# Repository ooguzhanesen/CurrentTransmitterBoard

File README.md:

# Current Transmitter Board
## Board Features

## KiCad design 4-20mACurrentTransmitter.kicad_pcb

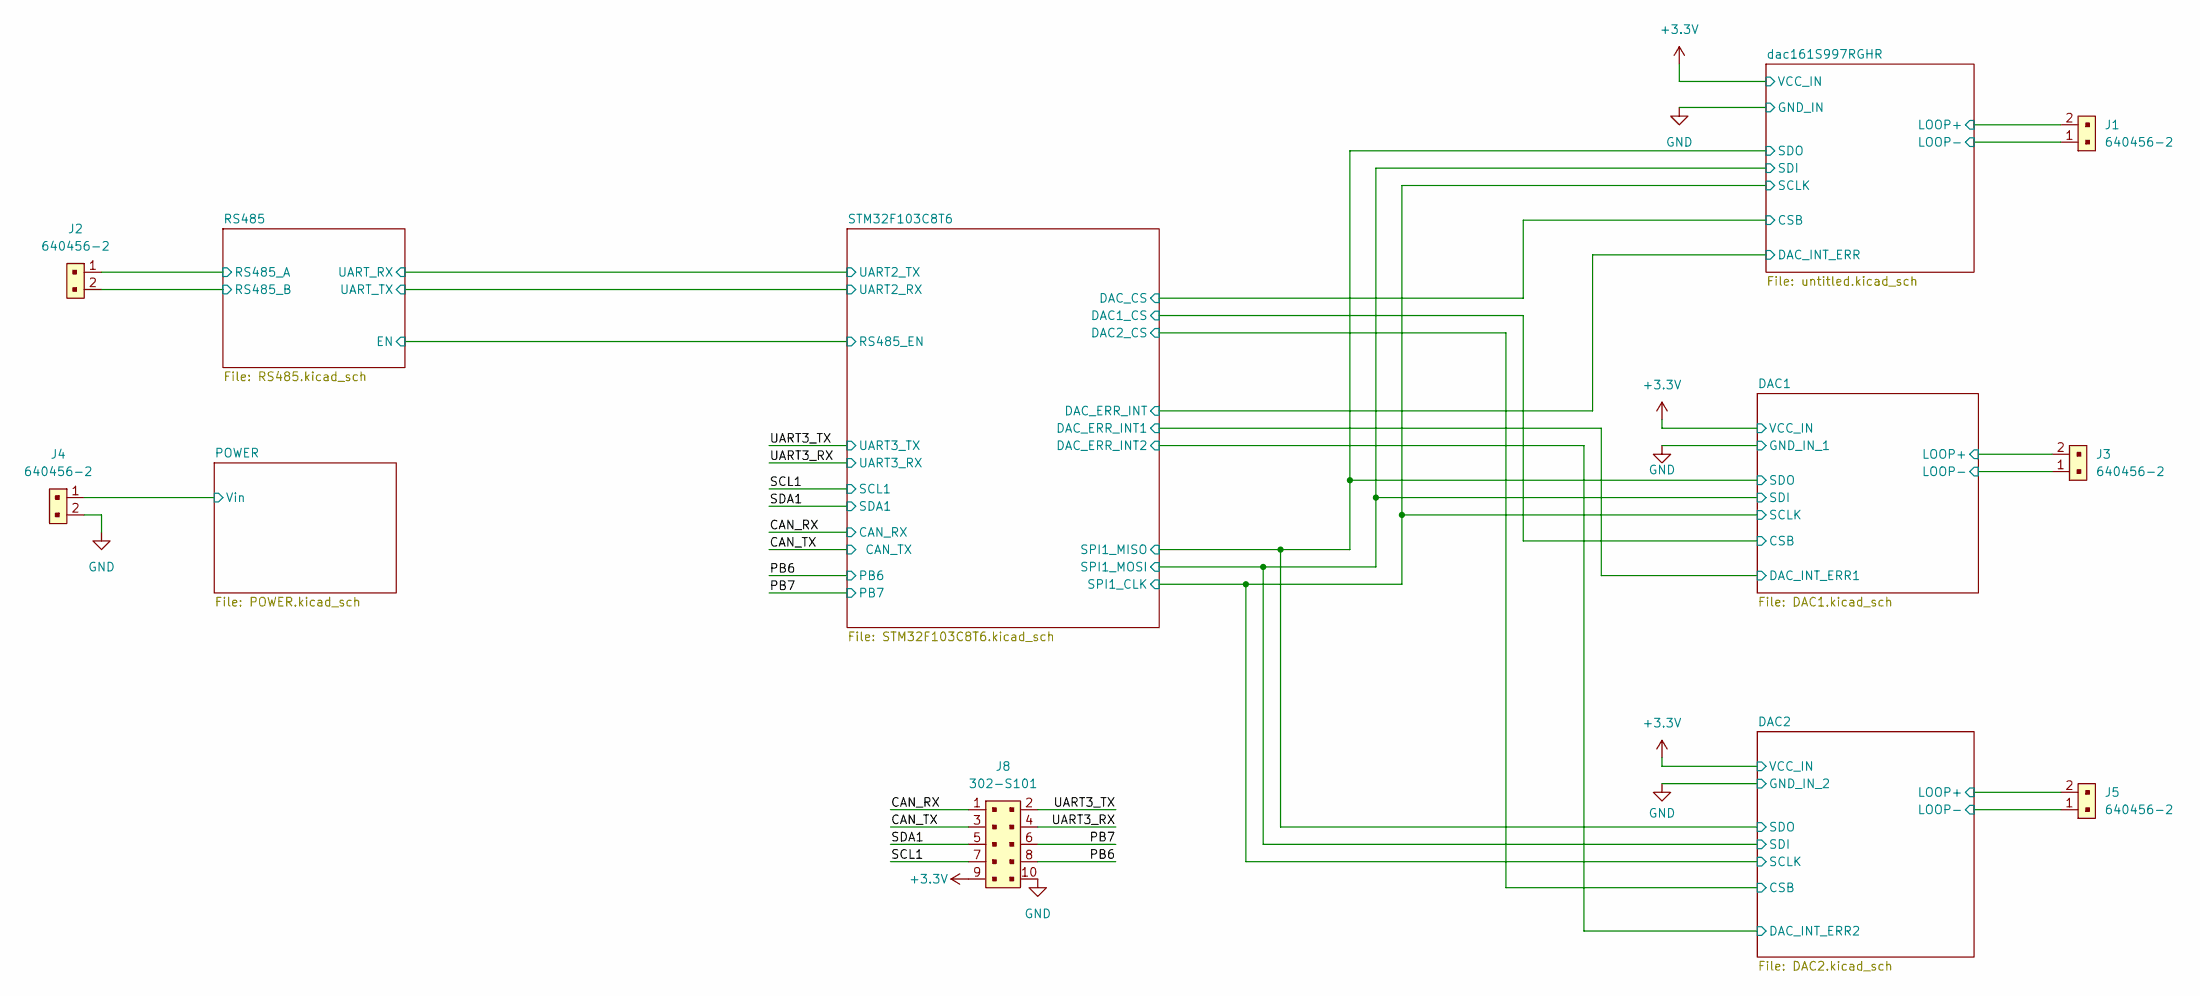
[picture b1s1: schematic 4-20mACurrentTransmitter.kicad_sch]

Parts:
J1, J2, J3, J4, J5: 640456-2; TerminalBlock_MetzConnect_Type101_RT01602HBWC_1x02_P5.08mm_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; MPN 640456-2; Digi-Key_PN A1921-ND
J8: 302-S101; PinHeader_2x5_P2.54mm_Drill1.2mm; MPN 302-S101; DigiKey ED1543-ND

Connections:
+3.3V: J8.9; also elsewhere on the board
/CAN_RX: J8.1; also elsewhere on the board
/CAN_TX: J8.3; also elsewhere on the board
/DAC1/LOOP+: J3.2; also elsewhere on the board
/DAC1/LOOP-: J3.1; also elsewhere on the board
/DAC2/LOOP+: J5.2; also elsewhere on the board
/DAC2/LOOP-: J5.1; also elsewhere on the board
/PB6: J8.8; also elsewhere on the board
/PB7: J8.6; also elsewhere on the board
/POWER/Vin: J4.1; also elsewhere on the board
/RS485/RS485_A: J2.1; also elsewhere on the board
/RS485/RS485_B: J2.2; also elsewhere on the board
/SCL1: J8.7; also elsewhere on the board
/SDA1: J8.5; also elsewhere on the board
/UART3_RX: J8.4; also elsewhere on the board
/UART3_TX: J8.2; also elsewhere on the board
/dac161S997RGHR/LOOP+: J1.2; also elsewhere on the board
/dac161S997RGHR/LOOP-: J1.1; also elsewhere on the board

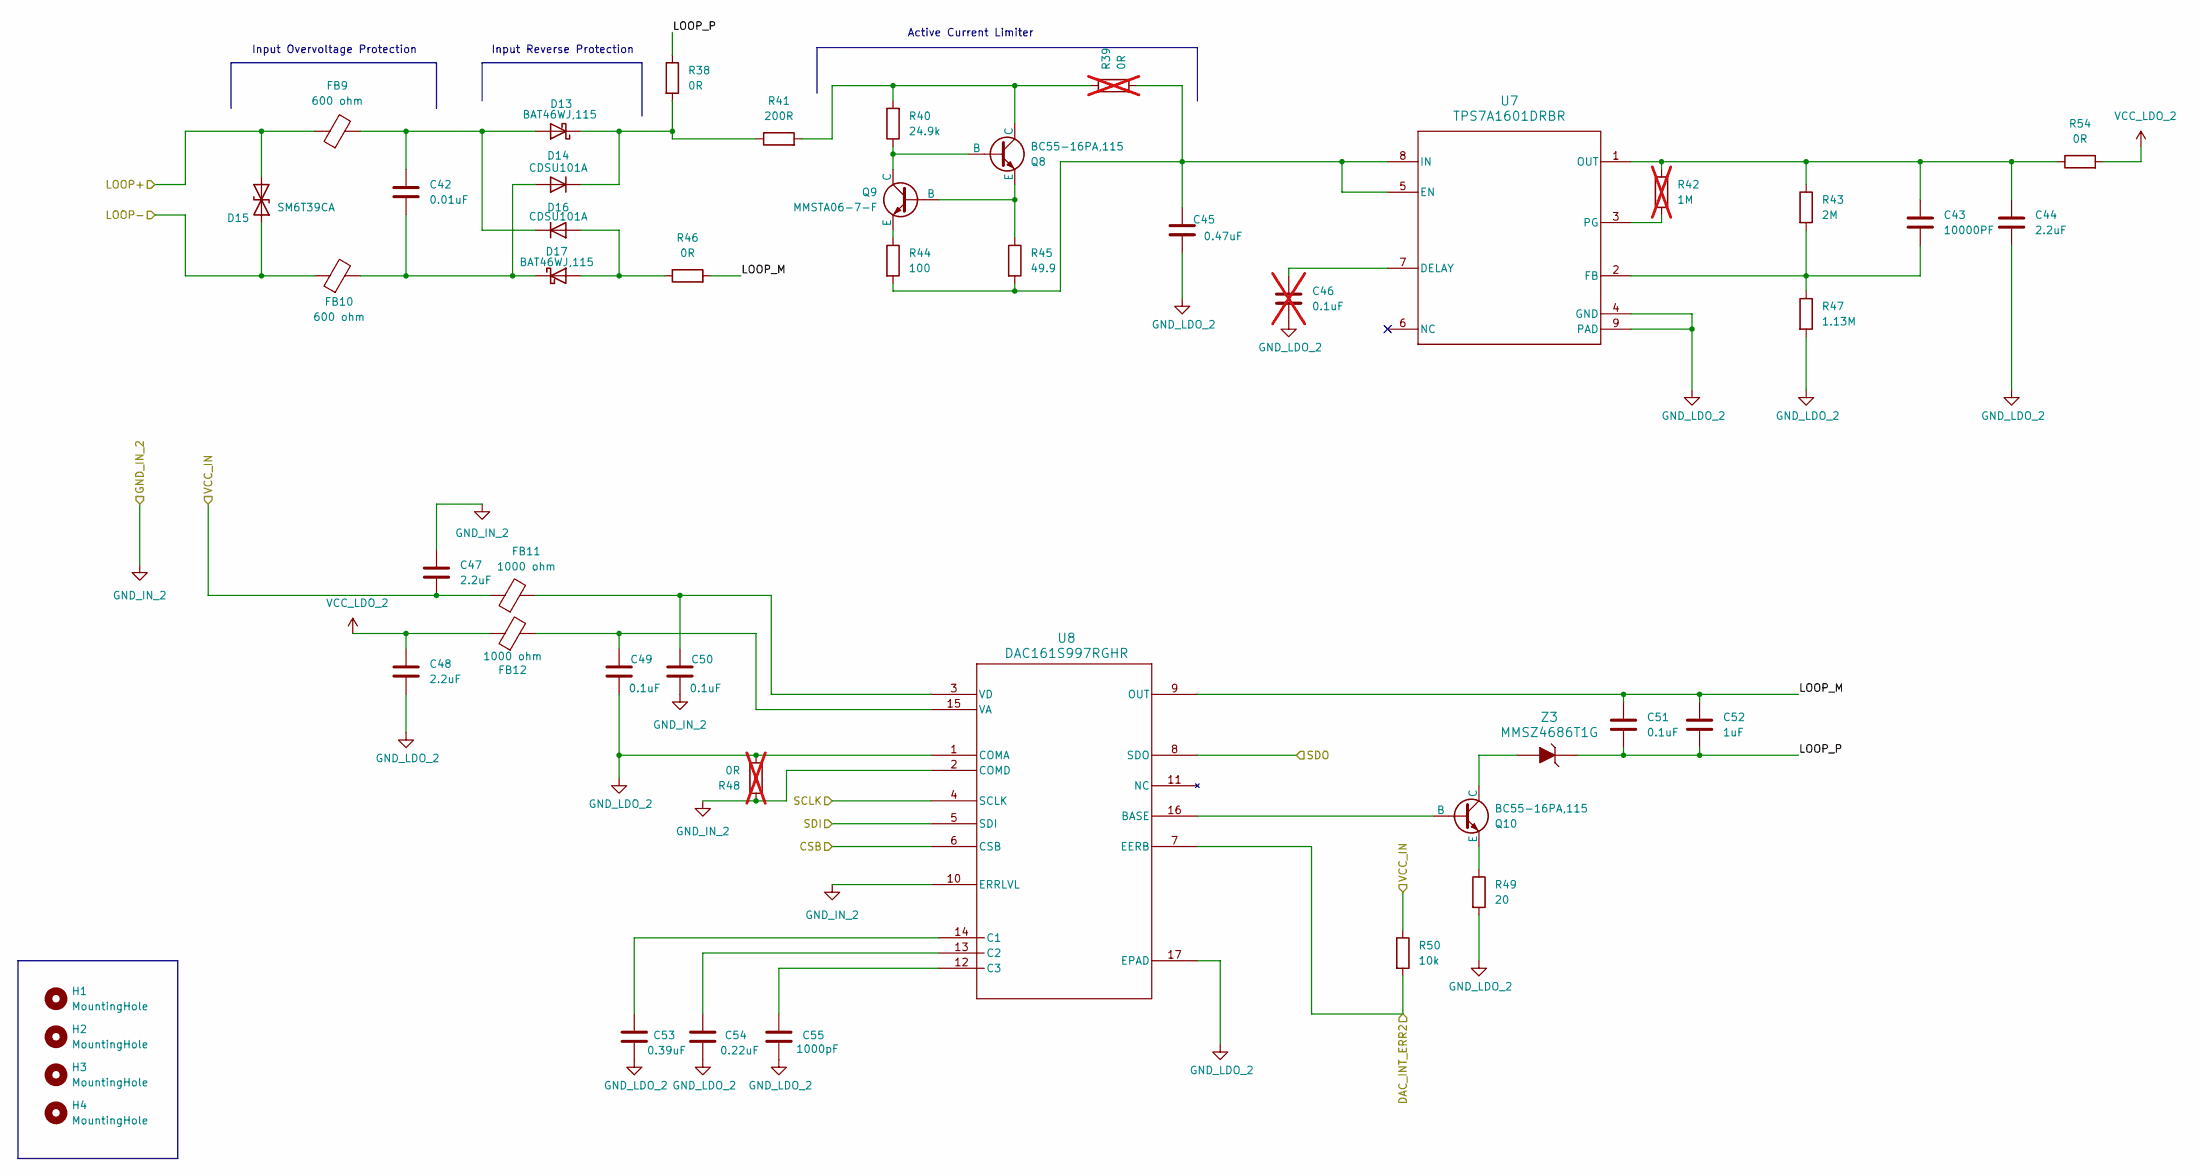
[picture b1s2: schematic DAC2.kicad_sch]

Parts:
C42: 0.01uF; C_0603_1608Metric; DIGIKEY 445-1304-2-ND
C43: 10000PF; C_0402_1005Metric; DIGIKEY 490-6296-2-ND
C44, C47, C48: 2.2uF; C_0402_1005Metric; DIGIKEY 445-9085-2-ND
C45: 0.47uF; C_0805_2012Metric; DIGIKEY 490-3326-2-ND
C46: 0.1uF; C_1206_3216Metric; DIGIKEY 478-KGM31DR72A104JUTR-ND; not fitted
C49, C50: 0.1uF; C_0402_1005Metric; DIGIKEY 445-1266-2-ND
C51: 0.1uF; C_1206_3216Metric; DIGIKEY 478-KGM31DR72A104JUTR-ND
C52: 1uF; C_1206_3216Metric; DIGIKEY 490-3909-2-ND
C53: 0.39uF; C_0402_1005Metric; DIGIKEY 490-8253-2-ND
C54: 0.22uF; C_0402_1005Metric; DIGIKEY 490-5407-2-ND
C55: 1000pF; C_0402_1005Metric; DIGIKEY 490-6285-2-ND
D13, D17: BAT46WJ,115; D_SOD-323F; DIGIKEY 1727-4817-2-ND
D14, D16: CDSU101A; LED_CDSU101A; DIGIKEY 641-1002-2-ND
D15: SM6T39CA; D_SMB; DIGIKEY 497-6498-2-ND
FB9, FB10: 600 ohm; R_1206_3216Metric; DIGIKEY 240-2405-2-ND
FB11, FB12: 1000 ohm; R_0402_1005Metric; DIGIKEY 490-3999-2-ND
H1, H2, H3, H4: MountingHole; MountingHole_3.2mm_M3_DIN965_Pad
Q8, Q10: BC55-16PA,115; 3-HUSON(2X2); DIGIKEY 1727-2344-2-ND
Q9: MMSTA06-7-F; SOT-323; DIGIKEY MMSTA06-FDITR-ND
R38, R46, R54: 0R; R_0603_1608Metric; DIGIKEY 541-0.0GTR-ND
R39, R48: 0R; R_0603_1608Metric; DIGIKEY 541-0.0GTR-ND; not fitted
R40: 24.9k; R_0603_1608Metric; DIGIKEY 541-4028-2-ND
R41: 200R; R_1206_3216Metric; DIGIKEY 541-200FTR-ND
R42: 1M; R_0402_1005Metric; DIGIKEY 541-4119-2-ND; not fitted
R43: 2M; R_0402_1005Metric; DIGIKEY 541-4066-2-ND
R44: 100; R_0603_1608Metric; DIGIKEY 541-100STR-ND
R45: 49.9; R_1206_3216Metric; DIGIKEY 541-4185-2-ND
R47: 1.13M; R_0402_1005Metric; DIGIKEY 541-1.13MLTR-ND
R49: 20; R_0603_1608Metric; DIGIKEY 541-20.0HTR-ND
R50: 10k; R_0402_1005Metric; DIGIKEY 311-10KJRTR-ND
U7: TPS7A1601DRBR; DRB0008B; DIGIKEY 96-40969-2-ND
U8: DAC161S997RGHR; RGH16_TEX; DIGIKEY 296-40022-2-ND
Z3: MMSZ4686T1G; SOD-123; DIGIKEY MMSZ4686T1GOSTR-ND

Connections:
+3.3V: C47.2, FB11.1, R50.1; also elsewhere on the board
/DAC1/SCLK: U8.4 (SCLK); also elsewhere on the board
/DAC1/SDI: U8.5 (SDI); also elsewhere on the board
/DAC1/SDO: U8.8 (SDO); also elsewhere on the board
/DAC2/CSB: U8.6 (CSB); also elsewhere on the board
/DAC2/DAC_INT_ERR2: R50.2, U8.7 (EERB); also elsewhere on the board
/DAC2/LOOP+: D15.1 (A1), FB9.1; also elsewhere on the board
/DAC2/LOOP-: D15.2 (A2), FB10.1; also elsewhere on the board
/DAC2/LOOP_M: C51.1, C52.1, R46.2, U8.9 (OUT)
/DAC2/LOOP_P: C51.2, C52.2, R38.1, Z3.K
GND_LDO_2: C44.2, C45.2, C46.2, C48.2, C49.2, C53.2, C54.2, C55.2, R47.2, R48.2, R49.2, U7.4 (GND), U7.9 (PAD), U8.1 (COMA), U8.17 (EPAD)
unnamed: C42.1, D13.2 (A), D16.1 (K), FB9.2
unnamed: D13.1 (K), D14.1 (K), R38.2, R41.1
unnamed: C42.2, D14.2 (A), D17.1 (K), FB10.2
unnamed: D16.2 (A), D17.2 (A), R46.1
unnamed: Q8.2 (B), Q9.1 (C), R40.1
unnamed: Q8.1 (C), R39.1, R40.2, R41.2
unnamed: Q8.3 (E), Q9.2 (B), R45.1
unnamed: Q9.3 (E), R44.1
unnamed: Q10.2 (B), U8.16 (BASE)
unnamed: Q10.1 (C), Z3.A
unnamed: Q10.3 (E), R49.1
unnamed: C46.1, U7.7 (DELAY)
unnamed: C45.1, R39.2, R44.2, R45.2, U7.5 (EN), U7.8 (IN)
unnamed: C43.2, R43.2, R47.1, U7.2 (FB)
unnamed: C43.1, C44.1, R42.1, R43.1, R54.1, U7.1 (OUT)
unnamed: R42.2, U7.3 (PG)
unnamed: C53.1, U8.14 (C1)
unnamed: C54.1, U8.13 (C2)
unnamed: C55.1, U8.12 (C3)
unnamed: C49.1, FB12.2, U8.15 (VA)
unnamed: C50.1, FB11.2, U8.3 (VD)
VCC_LDO_2: C48.1, FB12.1, R54.2

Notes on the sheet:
Input Overvoltage Protection
Input Reverse Protection
Active Current Limiter

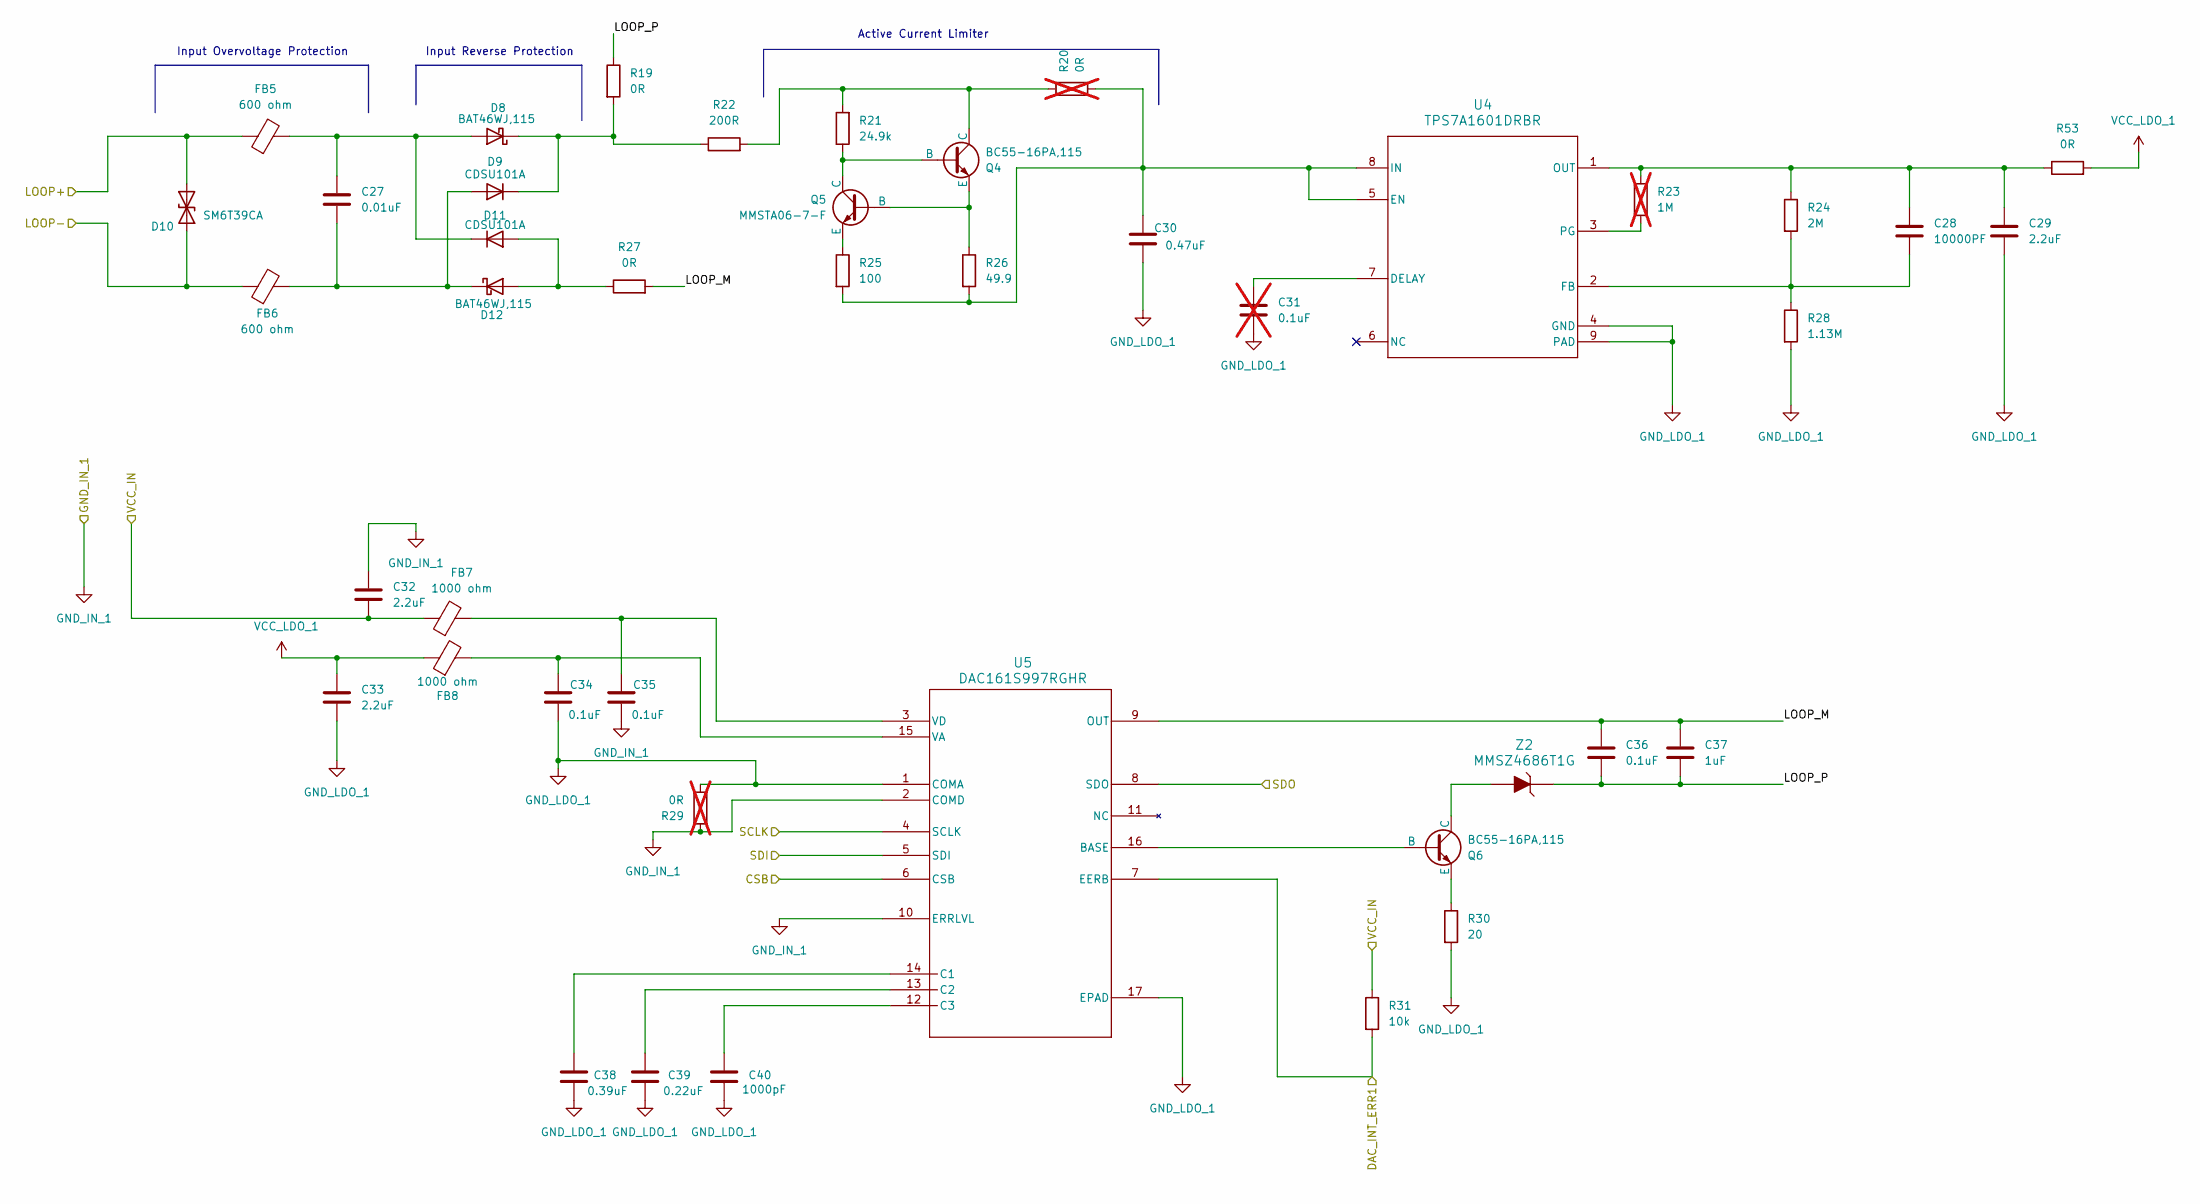
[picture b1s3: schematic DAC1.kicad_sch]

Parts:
C27: 0.01uF; C_0603_1608Metric; DIGIKEY 445-1304-2-ND
C28: 10000PF; C_0402_1005Metric; DIGIKEY 490-6296-2-ND
C29, C32, C33: 2.2uF; C_0402_1005Metric; DIGIKEY 445-9085-2-ND
C30: 0.47uF; C_0805_2012Metric; DIGIKEY 490-3326-2-ND
C31: 0.1uF; C_1206_3216Metric; DIGIKEY 478-KGM31DR72A104JUTR-ND; not fitted
C34, C35: 0.1uF; C_0402_1005Metric; DIGIKEY 445-1266-2-ND
C36: 0.1uF; C_1206_3216Metric; DIGIKEY 478-KGM31DR72A104JUTR-ND
C37: 1uF; C_1206_3216Metric; DIGIKEY 490-3909-2-ND
C38: 0.39uF; C_0402_1005Metric; DIGIKEY 490-8253-2-ND
C39: 0.22uF; C_0402_1005Metric; DIGIKEY 490-5407-2-ND
C40: 1000pF; C_0402_1005Metric; DIGIKEY 490-6285-2-ND
D8, D12: BAT46WJ,115; D_SOD-323F; DIGIKEY 1727-4817-2-ND
D9, D11: CDSU101A; LED_CDSU101A; DIGIKEY 641-1002-2-ND
D10: SM6T39CA; D_SMB; DIGIKEY 497-6498-2-ND
FB5, FB6: 600 ohm; R_1206_3216Metric; DIGIKEY 240-2405-2-ND
FB7, FB8: 1000 ohm; R_0402_1005Metric; DIGIKEY 490-3999-2-ND
Q4, Q6: BC55-16PA,115; 3-HUSON(2X2); DIGIKEY 1727-2344-2-ND
Q5: MMSTA06-7-F; SOT-323; DIGIKEY MMSTA06-FDITR-ND
R19, R27, R53: 0R; R_0603_1608Metric; DIGIKEY 541-0.0GTR-ND
R20, R29: 0R; R_0603_1608Metric; DIGIKEY 541-0.0GTR-ND; not fitted
R21: 24.9k; R_0603_1608Metric; DIGIKEY 541-4028-2-ND
R22: 200R; R_1206_3216Metric; DIGIKEY 541-200FTR-ND
R23: 1M; R_0402_1005Metric; DIGIKEY 541-4119-2-ND; not fitted
R24: 2M; R_0402_1005Metric; DIGIKEY 541-4066-2-ND
R25: 100; R_0603_1608Metric; DIGIKEY 541-100STR-ND
R26: 49.9; R_1206_3216Metric; DIGIKEY 541-4185-2-ND
R28: 1.13M; R_0402_1005Metric; DIGIKEY 541-1.13MLTR-ND
R30: 20; R_0603_1608Metric; DIGIKEY 541-20.0HTR-ND
R31: 10k; R_0402_1005Metric; DIGIKEY 311-10KJRTR-ND
U4: TPS7A1601DRBR; DRB0008B; DIGIKEY 96-40969-2-ND
U5: DAC161S997RGHR; RGH16_TEX; DIGIKEY 296-40022-2-ND
Z2: MMSZ4686T1G; SOD-123; DIGIKEY MMSZ4686T1GOSTR-ND

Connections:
+3.3V: C32.2, FB7.1, R31.1; also elsewhere on the board
/DAC1/CSB: U5.6 (CSB); also elsewhere on the board
/DAC1/DAC_INT_ERR1: R31.2, U5.7 (EERB); also elsewhere on the board
/DAC1/LOOP+: D10.1 (A1), FB5.1; also elsewhere on the board
/DAC1/LOOP-: D10.2 (A2), FB6.1; also elsewhere on the board
/DAC1/LOOP_M: C36.1, C37.1, R27.2, U5.9 (OUT)
/DAC1/LOOP_P: C36.2, C37.2, R19.1, Z2.K
/DAC1/SCLK: U5.4 (SCLK); also elsewhere on the board
/DAC1/SDI: U5.5 (SDI); also elsewhere on the board
/DAC1/SDO: U5.8 (SDO); also elsewhere on the board
GND_LDO_1: C29.2, C30.2, C31.2, C33.2, C34.2, C38.2, C39.2, C40.2, R28.2, R29.2, R30.2, U4.4 (GND), U4.9 (PAD), U5.1 (COMA), U5.17 (EPAD)
unnamed: D8.1 (K), D9.1 (K), R19.2, R22.1
unnamed: D11.2 (A), D12.2 (A), R27.1
unnamed: C27.1, D8.2 (A), D11.1 (K), FB5.2
unnamed: C27.2, D9.2 (A), D12.1 (K), FB6.2
unnamed: Q4.2 (B), Q5.1 (C), R21.1
unnamed: Q4.1 (C), R20.1, R21.2, R22.2
unnamed: Q4.3 (E), Q5.2 (B), R26.1
unnamed: Q5.3 (E), R25.1
unnamed: Q6.2 (B), U5.16 (BASE)
unnamed: Q6.1 (C), Z2.A
unnamed: Q6.3 (E), R30.1
unnamed: C31.1, U4.7 (DELAY)
unnamed: C30.1, R20.2, R25.2, R26.2, U4.5 (EN), U4.8 (IN)
unnamed: C28.2, R24.2, R28.1, U4.2 (FB)
unnamed: C28.1, C29.1, R23.1, R24.1, R53.1, U4.1 (OUT)
unnamed: R23.2, U4.3 (PG)
unnamed: C38.1, U5.14 (C1)
unnamed: C39.1, U5.13 (C2)
unnamed: C40.1, U5.12 (C3)
unnamed: C34.1, FB8.2, U5.15 (VA)
unnamed: C35.1, FB7.2, U5.3 (VD)
VCC_LDO_1: C33.1, FB8.1, R53.2

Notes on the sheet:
Input Overvoltage Protection
Input Reverse Protection
Active Current Limiter

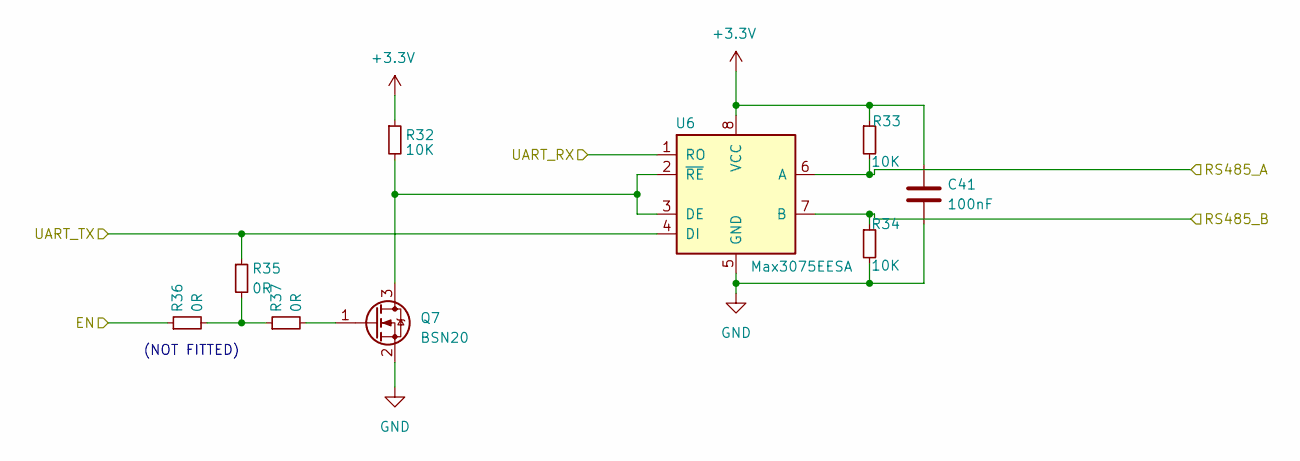
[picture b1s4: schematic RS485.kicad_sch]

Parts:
C41: 100nF; C_0402_1005Metric; DIGIKEY 3372-0402B104K500HITR-ND
Q7: BSN20; SOT-23; DIGIKEY BSN20-7DITR-ND
R32, R33, R34: 10K; R_0603_1608Metric; DIGIKEY 311-10.0KHRTR-ND
R35, R36, R37: 0R; R_0603_1608Metric; DIGIKEY 541-0.0GTR-ND
U6: Max3075EESA; SOIC-8_3.9x4.9mm_P1.27mm; DIGIKEY MAX3075EESA+-ND

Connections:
+3.3V: C41.1, R32.1, R33.1, U6.8 (VCC); also elsewhere on the board
/RS485/EN: R36.1; also elsewhere on the board
/RS485/RS485_A: R33.2, U6.6 (A); also elsewhere on the board
/RS485/RS485_B: R34.1, U6.7 (B); also elsewhere on the board
/RS485/UART_RX: U6.1 (RO); also elsewhere on the board
/RS485/UART_TX: R35.1, U6.4 (DI); also elsewhere on the board
unnamed: Q7.3 (D), R32.2, U6.2 (~RE), U6.3 (DE)
unnamed: Q7.1 (G), R37.2
unnamed: R35.2, R36.2, R37.1

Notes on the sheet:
(NOT FITTED)

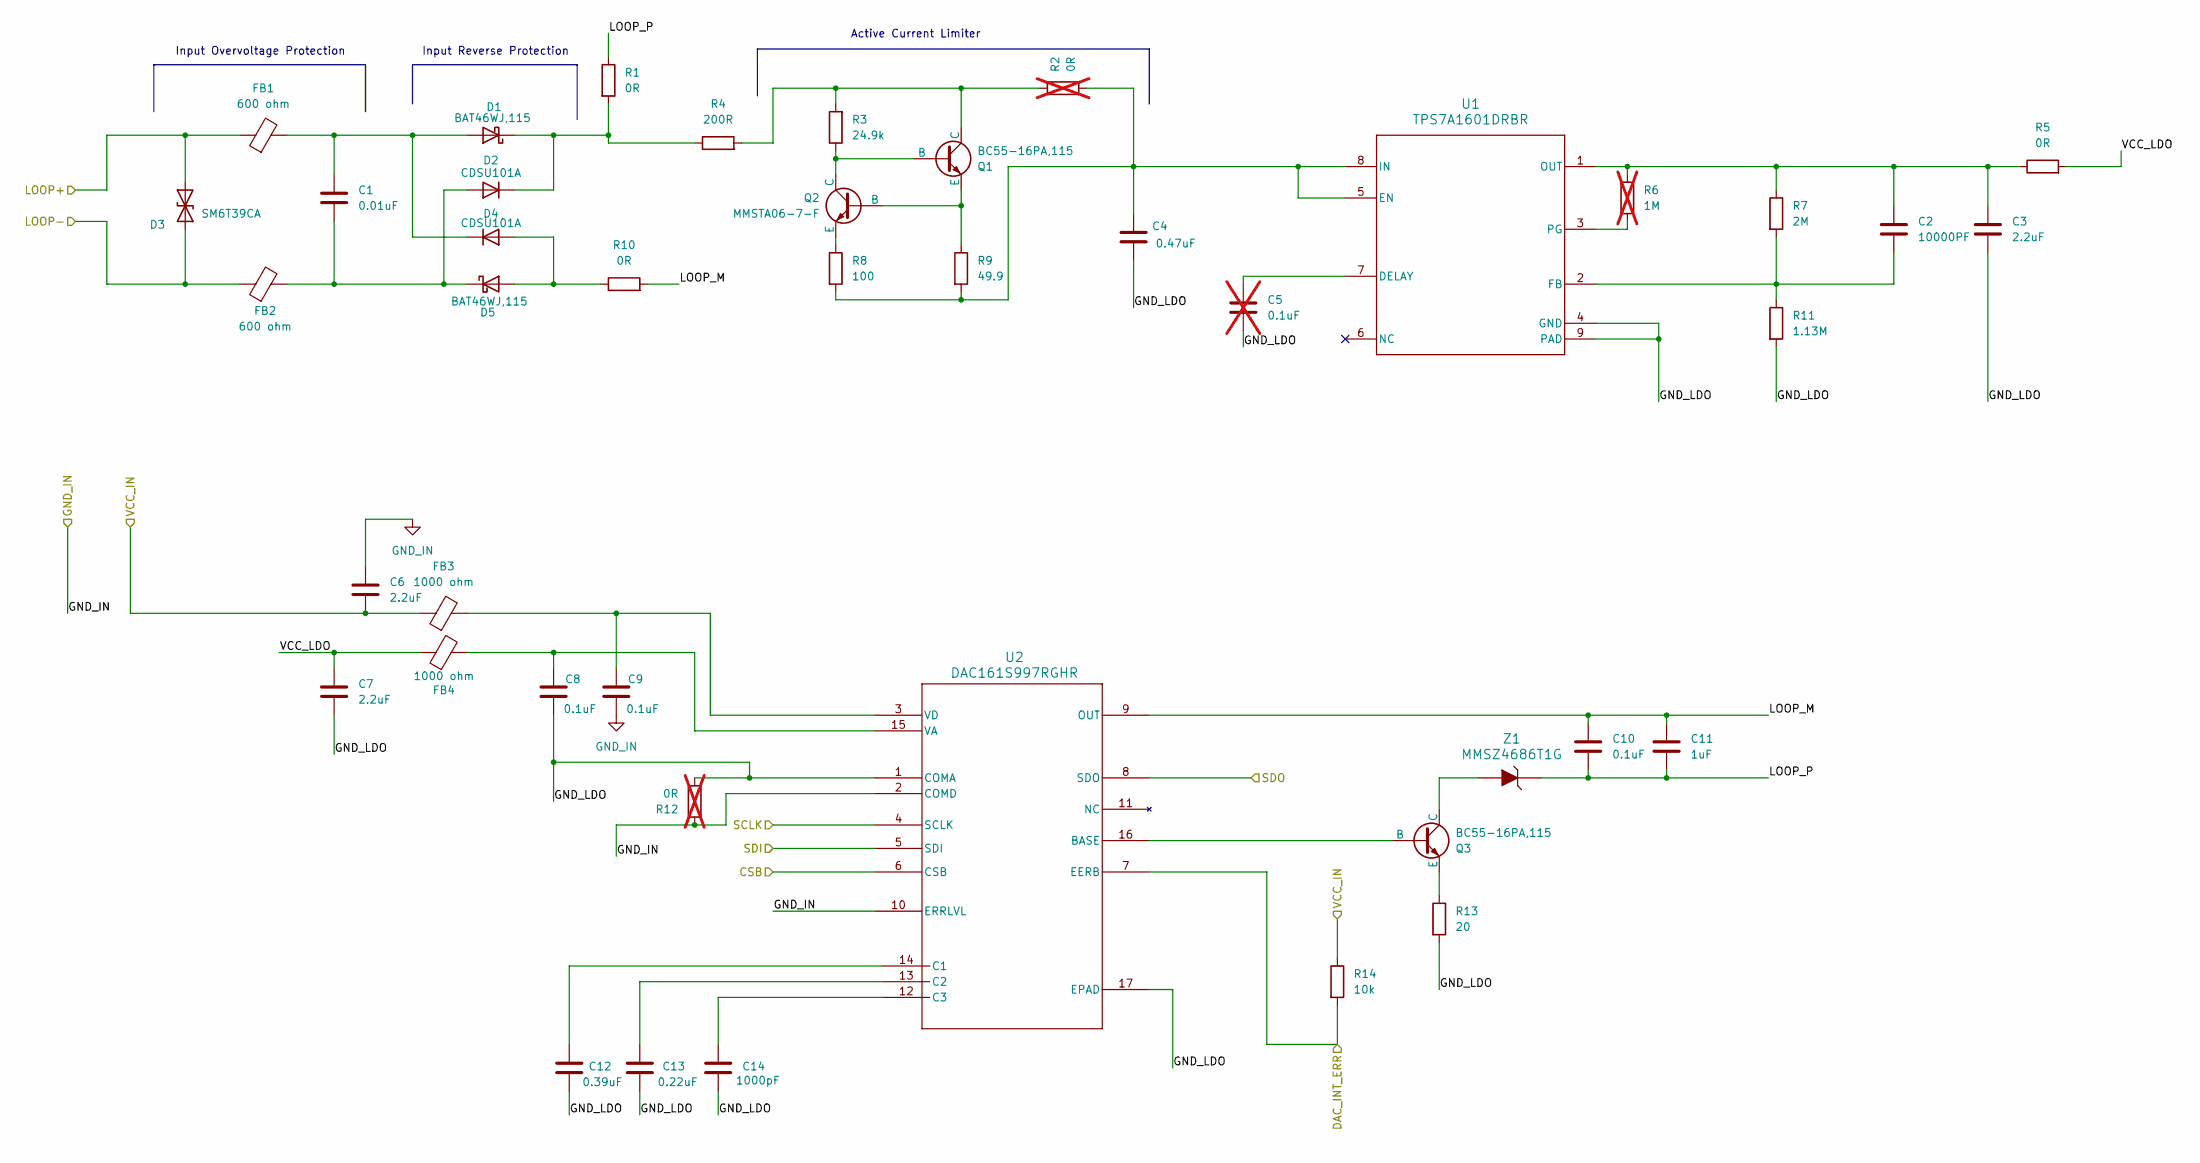
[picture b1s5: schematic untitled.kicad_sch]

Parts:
C1: 0.01uF; C_0603_1608Metric; DIGIKEY 445-1304-2-ND
C2: 10000PF; C_0402_1005Metric; DIGIKEY 490-6296-2-ND
C3, C6, C7: 2.2uF; C_0402_1005Metric; DIGIKEY 445-9085-2-ND
C4: 0.47uF; C_0805_2012Metric; DIGIKEY 490-3326-2-ND
C5: 0.1uF; C_1206_3216Metric; DIGIKEY 478-KGM31DR72A104JUTR-ND; not fitted
C8, C9: 0.1uF; C_0402_1005Metric; DIGIKEY 445-1266-2-ND
C10: 0.1uF; C_1206_3216Metric; DIGIKEY 478-KGM31DR72A104JUTR-ND
C11: 1uF; C_1206_3216Metric; DIGIKEY 490-3909-2-ND
C12: 0.39uF; C_0402_1005Metric; DIGIKEY 490-8253-2-ND
C13: 0.22uF; C_0402_1005Metric; DIGIKEY 490-5407-2-ND
C14: 1000pF; C_0402_1005Metric; DIGIKEY 490-6285-2-ND
D1, D5: BAT46WJ,115; D_SOD-323F; DIGIKEY 1727-4817-2-ND
D2, D4: CDSU101A; LED_CDSU101A; DIGIKEY 641-1002-2-ND
D3: SM6T39CA; D_SMB; DIGIKEY 497-6498-2-ND
FB1, FB2: 600 ohm; R_1206_3216Metric; DIGIKEY 240-2405-2-ND
FB3, FB4: 1000 ohm; R_0402_1005Metric; DIGIKEY 490-3999-2-ND
Q1, Q3: BC55-16PA,115; 3-HUSON(2X2); DIGIKEY 1727-2344-2-ND
Q2: MMSTA06-7-F; SOT-323; DIGIKEY MMSTA06-FDITR-ND
R1, R5, R10: 0R; R_0603_1608Metric; DIGIKEY 541-0.0GTR-ND
R2, R12: 0R; R_0603_1608Metric; DIGIKEY 541-0.0GTR-ND; not fitted
R3: 24.9k; R_0603_1608Metric; DIGIKEY 541-4028-2-ND
R4: 200R; R_1206_3216Metric; DIGIKEY 541-200FTR-ND
R6: 1M; R_0402_1005Metric; DIGIKEY 541-4119-2-ND; not fitted
R7: 2M; R_0402_1005Metric; DIGIKEY 541-4066-2-ND
R8: 100; R_0603_1608Metric; DIGIKEY 541-100STR-ND
R9: 49.9; R_1206_3216Metric; DIGIKEY 541-4185-2-ND
R11: 1.13M; R_0402_1005Metric; DIGIKEY 541-1.13MLTR-ND
R13: 20; R_0603_1608Metric; DIGIKEY 541-20.0HTR-ND
R14: 10k; R_0402_1005Metric; DIGIKEY 311-10KJRTR-ND
U1: TPS7A1601DRBR; DRB0008B; DIGIKEY 96-40969-2-ND
U2: DAC161S997RGHR; RGH16_TEX; DIGIKEY 296-40022-2-ND
Z1: MMSZ4686T1G; SOD-123; DIGIKEY MMSZ4686T1GOSTR-ND

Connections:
+3.3V: C6.2, FB3.1, R14.1; also elsewhere on the board
/DAC1/SCLK: U2.4 (SCLK); also elsewhere on the board
/DAC1/SDI: U2.5 (SDI); also elsewhere on the board
/DAC1/SDO: U2.8 (SDO); also elsewhere on the board
/STM32F103C8T6/DAC_CS: U2.6 (CSB); also elsewhere on the board
/STM32F103C8T6/DAC_ERR_INT: R14.2, U2.7 (EERB); also elsewhere on the board
/dac161S997RGHR/GND_LDO: C3.2, C4.2, C5.2, C7.2, C8.2, C12.2, C13.2, C14.2, R11.2, R12.2, R13.2, U1.4 (GND), U1.9 (PAD), U2.1 (COMA), U2.17 (EPAD)
/dac161S997RGHR/LOOP+: D3.1 (A1), FB1.1; also elsewhere on the board
/dac161S997RGHR/LOOP-: D3.2 (A2), FB2.1; also elsewhere on the board
/dac161S997RGHR/LOOP_M: C10.1, C11.1, R10.2, U2.9 (OUT)
/dac161S997RGHR/LOOP_P: C10.2, C11.2, R1.1, Z1.K
/dac161S997RGHR/VCC_LDO: C7.1, FB4.1, R5.2
unnamed: C1.1, D1.2 (A), D4.1 (K), FB1.2
unnamed: D1.1 (K), D2.1 (K), R1.2, R4.1
unnamed: C1.2, D2.2 (A), D5.1 (K), FB2.2
unnamed: D4.2 (A), D5.2 (A), R10.1
unnamed: Q1.2 (B), Q2.1 (C), R3.1
unnamed: Q1.1 (C), R2.1, R3.2, R4.2
unnamed: Q1.3 (E), Q2.2 (B), R9.1
unnamed: Q2.3 (E), R8.1
unnamed: Q3.2 (B), U2.16 (BASE)
unnamed: Q3.1 (C), Z1.A
unnamed: Q3.3 (E), R13.1
unnamed: C5.1, U1.7 (DELAY)
unnamed: C4.1, R2.2, R8.2, R9.2, U1.5 (EN), U1.8 (IN)
unnamed: C2.2, R7.2, R11.1, U1.2 (FB)
unnamed: C2.1, C3.1, R5.1, R6.1, R7.1, U1.1 (OUT)
unnamed: R6.2, U1.3 (PG)
unnamed: C12.1, U2.14 (C1)
unnamed: C13.1, U2.13 (C2)
unnamed: C14.1, U2.12 (C3)
unnamed: C8.1, FB4.2, U2.15 (VA)
unnamed: C9.1, FB3.2, U2.3 (VD)

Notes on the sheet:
Active Current Limiter
Input Overvoltage Protection
Input Reverse Protection

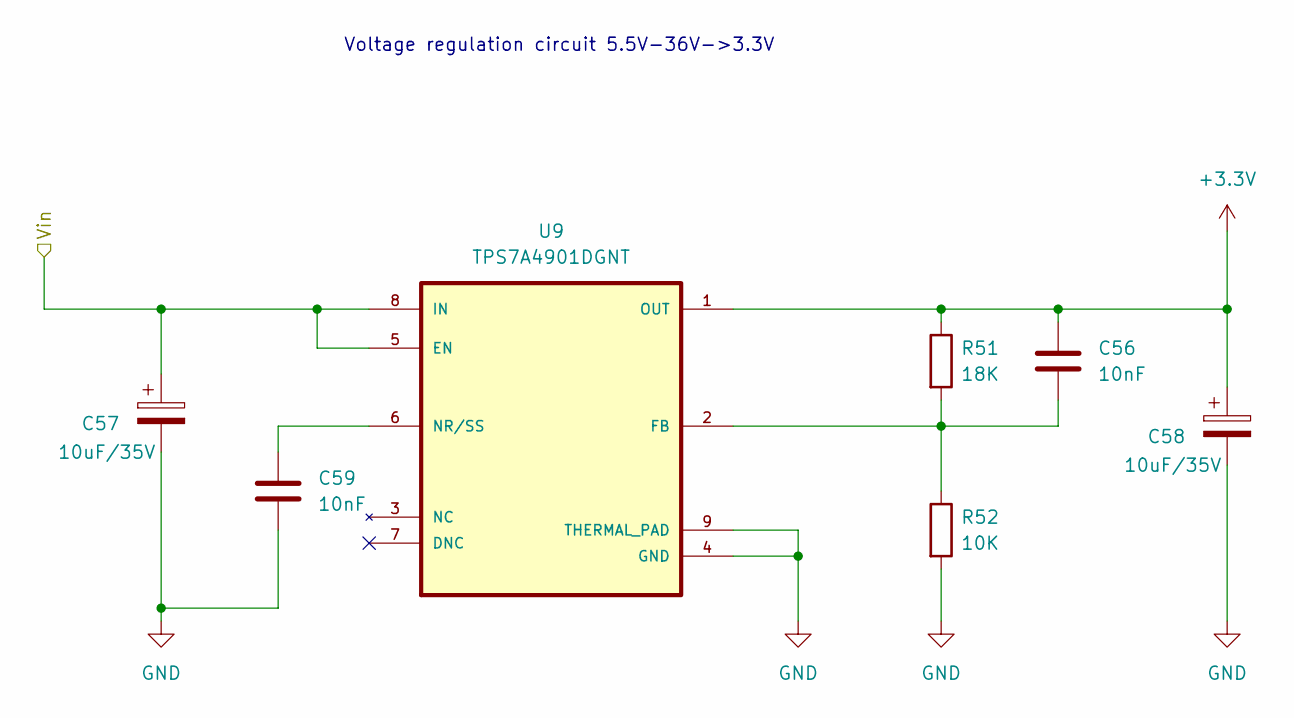
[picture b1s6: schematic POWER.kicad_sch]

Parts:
C56, C59: 10nF; C_0603_1608Metric; DIGIKEY 399-C0603C103K4RECTUTR-ND
C57, C58: 10uF/35V; CP_Elec_5x5.4; DIGIKEY 732-8295-2-ND
R51: 18K; R_0603_1608Metric; DIGIKEY 11-18KGRTR-ND
R52: 10K; R_0603_1608Metric; DIGIKEY 311-10.0KHRTR-ND
U9: TPS7A4901DGNT; SOP65P490X110-9N; DIGIKEY TPS7A4901DGNT

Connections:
+3.3V: C56.1, C58.1, R51.1, U9.1 (OUT); also elsewhere on the board
/POWER/Vin: C57.1, U9.5 (EN), U9.8 (IN); also elsewhere on the board
unnamed: C56.2, R51.2, R52.1, U9.2 (FB)
unnamed: C59.1, U9.6 (NR/SS)

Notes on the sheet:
Voltage regulation circuit 5.5V-36V->3.3V

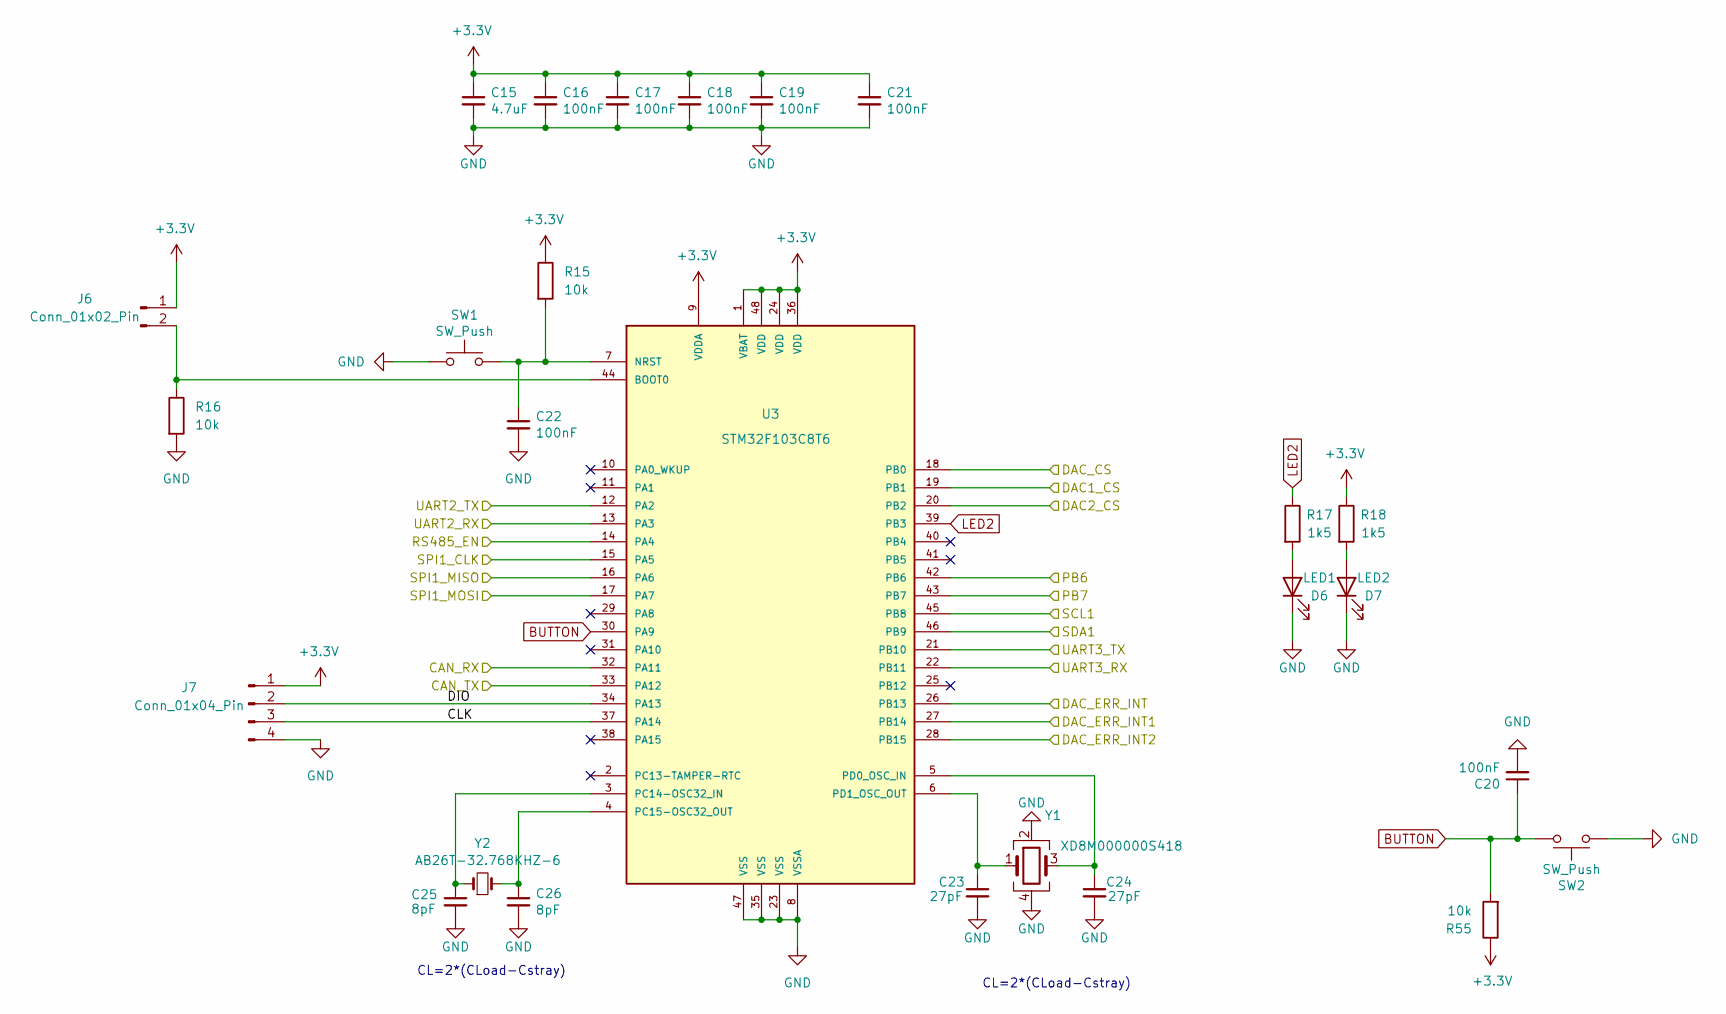
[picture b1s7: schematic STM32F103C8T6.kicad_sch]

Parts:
C15: 4.7uF; C_0603_1608Metric; DIGIKEY 3372-0603W475K100XDTR-ND
C16, C17, C18, C19, C20, C21, C22: 100nF; C_0402_1005Metric; DIGIKEY 3372-0402B104K500HITR-ND
C23, C24: 27pF; C_0402_1005Metric; DIGIKEY 2571-GMC04CG270G50NTTR-ND
C25, C26: 8pF; C_0402_1005Metric; DIGIKEY 490-8230-2-ND
D6: LED1; LED_0603_1608Metric; DIGIKEY 5859-YY0603YG-NN3S0-T2AR4TR-ND
D7: LED2; LED_0603_1608Metric; DIGIKEY 5859-YY0603RE-NN3S0-T2AR4TR-ND
J6: Conn_01x02_Pin; PinHeader_1x02_P2.54mm_Vertical; DIGIKEY 952-2262-ND
J7: Conn_01x04_Pin; PinHeader_1x04_P2.54mm_Vertical; DIGIKEY 732-5317-ND
R15, R16, R55: 10k; R_0402_1005Metric; DIGIKEY 311-10KJRTR-ND
R17, R18: 1k5; R_0603_1608Metric; DIGIKEY 311-1.5KGRTR-ND
SW1, SW2: SW_Push; pushbutton; DIGIKEY 1825910-6
U3: STM32F103C8T6; LQFP48_STM; DIGIKEY 497-6063-ND
Y1: XD8M000000S418; Crystal_SMD_EuroQuartz_MJ-4Pin_5.0x3.2mm; DIGIKEY XD8M000000S418
Y2: AB26T-32.768KHZ-6; XTAL_AB26T-32.768KHZ-6; DIGIKEY 535-AB26T-32.768KHZ-6TR-ND

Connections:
+3.3V: C15.1, C16.1, C17.1, C18.1, C19.1, C21.1, J6.1, J7.1, R15.1, R18.1, R55.1, U3.1 (VBAT), U3.9 (VDDA), U3.24 (VDD), U3.36 (VDD), U3.48 (VDD); also elsewhere on the board
/CAN_RX: U3.32 (PA11); also elsewhere on the board
/CAN_TX: U3.33 (PA12); also elsewhere on the board
/DAC1/CSB: U3.19 (PB1); also elsewhere on the board
/DAC1/DAC_INT_ERR1: U3.27 (PB14); also elsewhere on the board
/DAC1/SCLK: U3.15 (PA5); also elsewhere on the board
/DAC1/SDI: U3.17 (PA7); also elsewhere on the board
/DAC1/SDO: U3.16 (PA6); also elsewhere on the board
/DAC2/CSB: U3.20 (PB2); also elsewhere on the board
/DAC2/DAC_INT_ERR2: U3.28 (PB15); also elsewhere on the board
/PB6: U3.42 (PB6); also elsewhere on the board
/PB7: U3.43 (PB7); also elsewhere on the board
/RS485/EN: U3.14 (PA4); also elsewhere on the board
/RS485/UART_RX: U3.12 (PA2); also elsewhere on the board
/RS485/UART_TX: U3.13 (PA3); also elsewhere on the board
/SCL1: U3.45 (PB8); also elsewhere on the board
/SDA1: U3.46 (PB9); also elsewhere on the board
/STM32F103C8T6/CLK: J7.3, U3.37 (PA14)
/STM32F103C8T6/DAC_CS: U3.18 (PB0); also elsewhere on the board
/STM32F103C8T6/DAC_ERR_INT: U3.26 (PB13); also elsewhere on the board
/STM32F103C8T6/DIO: J7.2, U3.34 (PA13)
/UART3_RX: U3.22 (PB11); also elsewhere on the board
/UART3_TX: U3.21 (PB10); also elsewhere on the board
BUTTON: C20.1, R55.2, SW2.2, U3.30 (PA9)
LED2: R17.1, U3.39 (PB3)
unnamed: D6.2 (A), R17.2
unnamed: D7.2 (A), R18.2
unnamed: J6.2, R16.1, U3.44 (BOOT0)
unnamed: C22.1, R15.2, SW1.2, U3.7 (NRST)
unnamed: C25.1, U3.3 (PC14-OSC32_IN), Y2.1
unnamed: C26.1, U3.4 (PC15-OSC32_OUT), Y2.2
unnamed: C24.1, U3.5 (PD0_OSC_IN), Y1.3
unnamed: C23.1, U3.6 (PD1_OSC_OUT), Y1.1

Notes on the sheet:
CL=2*(CLoad-Cstray)

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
